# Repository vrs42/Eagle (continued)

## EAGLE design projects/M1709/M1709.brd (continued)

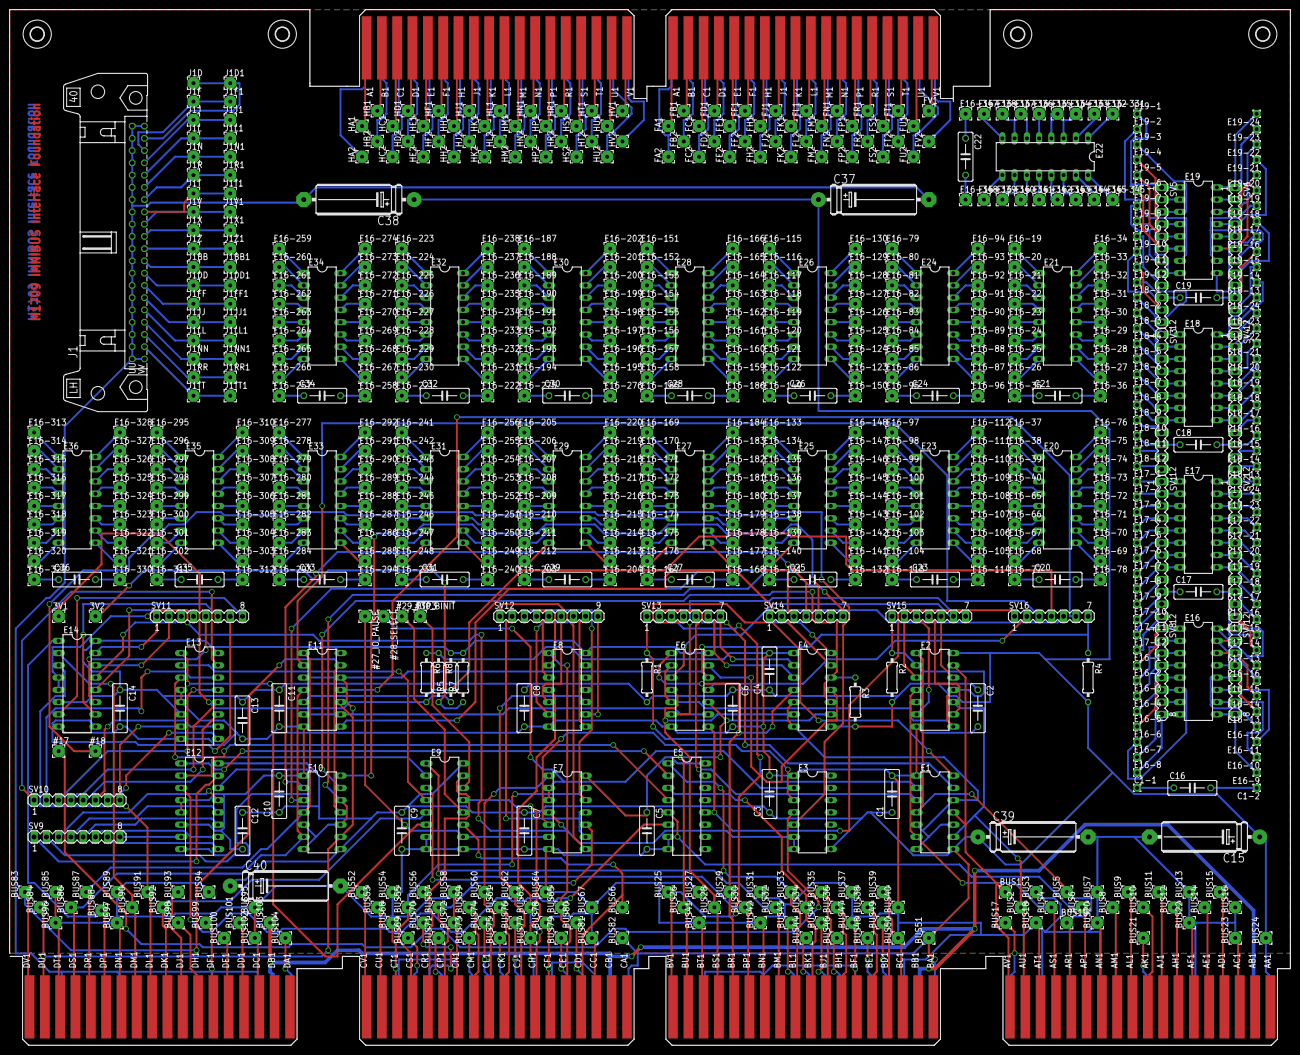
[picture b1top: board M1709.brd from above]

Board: 2 copper layers, 265.4 x 214.6 mm, 723 parts (0 on the bottom side), 633 nets.

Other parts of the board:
U$6, U$7, U$8, U$9: 2,8

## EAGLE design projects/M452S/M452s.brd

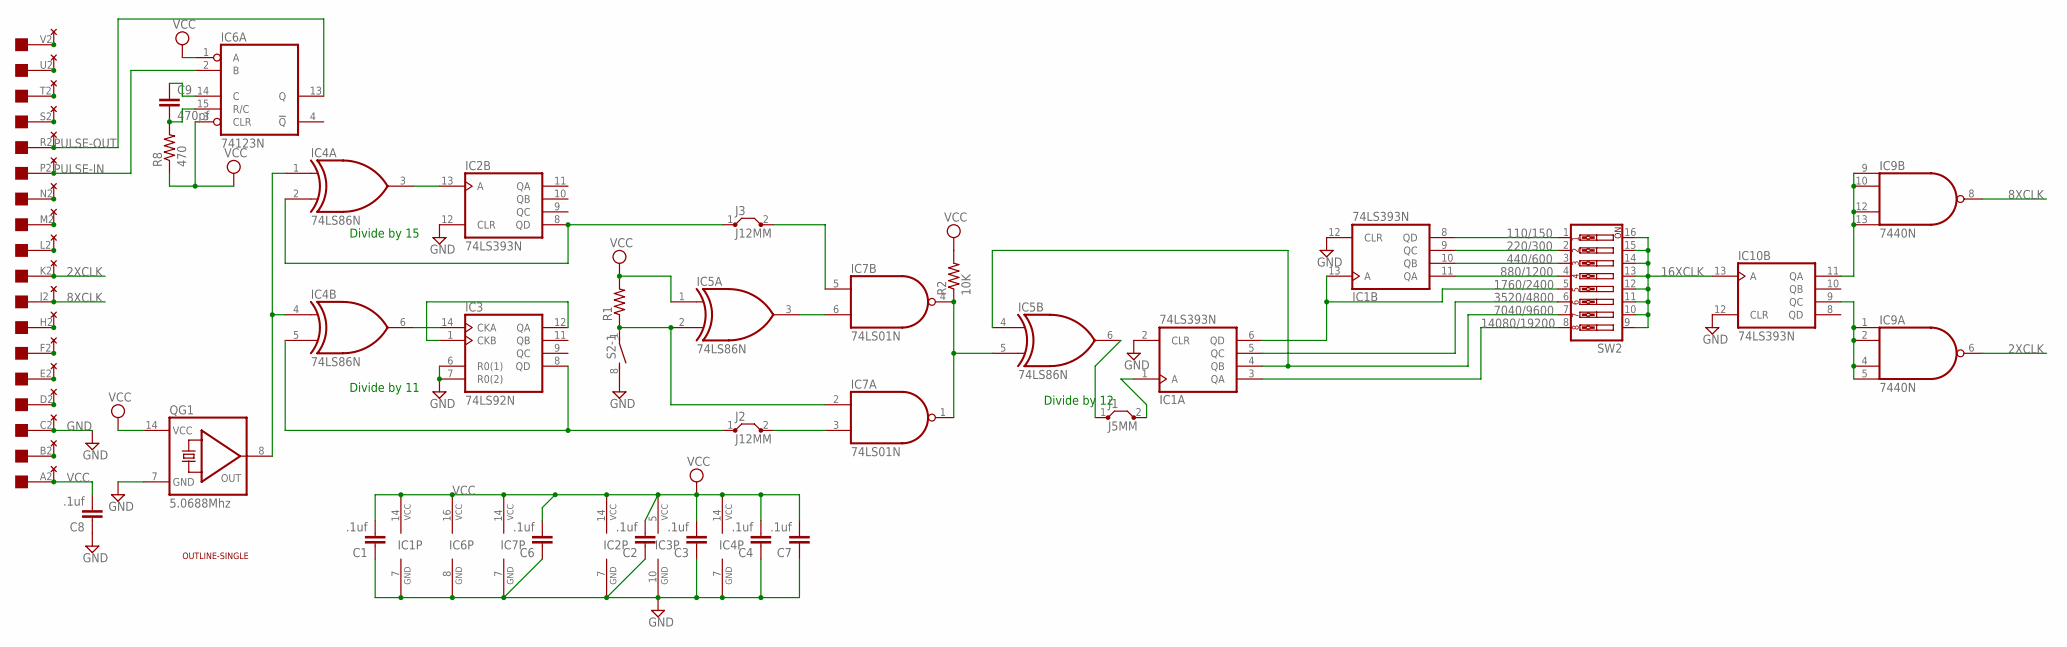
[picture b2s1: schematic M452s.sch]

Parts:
C1, C2, C3, C4, C6, C7, C8: .1uf; C050-025X075
C9: 470pf; C050-025X075
IC1, IC2, IC10: 74LS393N; DIL14
IC3: 74LS92N; DIL14
IC4, IC5: 74LS86N; DIL14
IC6: 74123N; DIL16
IC7: 74LS01N; DIL14
IC9: 7440N; DIL14
J1: J5MM; 05
J2, J3: J12MM; 12
QG1: 5.0688Mhz; DIL14S
R1: R-US_0204/7; 0204/7
R2: 10K; 0204/7
R8: 470; 0204/7
S2: DIP04S
SW2: SW_DIP-8; EDG-08
U$2: EDGE-1; EDGE-CON1
U$3: OUTLINE-SINGLE; SINGLE
U$4: THRU-HOLE1

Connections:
2XCLK: IC9.6 (O), U$2.K2, U$4.K2
8XCLK: IC9.8 (O), U$2.J2, U$4.J2
16XCLK: IC10.13 (A), SW2.9, SW2.10, SW2.11, SW2.12, SW2.13, SW2.14, SW2.15, SW2.16
110/150: IC1.8 (QD), SW2.1
220/300: IC1.9 (QC), SW2.2
440/600: IC1.10 (QB), SW2.3
880/1200: IC1.11 (QA), SW2.4
1760/2400: IC1.6 (QD), IC1.13 (A), SW2.5
3520/4800: IC1.5 (QC), SW2.6
7040/9600: IC1.4 (QB), IC5.4 (I0), SW2.7
14080/19200: IC1.3 (QA), SW2.8
GND: C1.1, C2.1, C3.1, C4.1, C6.1, C7.1, C8.1, IC1.2 (CLR), IC1.7 (GND), IC1.12 (CLR), IC2.7 (GND), IC2.12 (CLR), IC3.6 (R0(1)), IC3.7 (R0(2)), IC3.10 (GND), IC4.7 (GND), IC5.7 (GND), IC6.8 (GND), IC7.7 (GND), IC9.7 (GND), IC10.7 (GND), IC10.12 (CLR), QG1.7 (GND), S2.8 (2), U$2.C2, U$4.C2
unnamed: IC4.1 (I0), IC4.4 (I0), QG1.8 (OUT)
unnamed: IC2.8 (QD), IC4.2 (I1), J3.1
unnamed: IC3.8 (QD), IC4.5 (I1), J2.1
unnamed: IC3.1 (CKB), IC3.12 (QA)
unnamed: IC3.14 (CKA), IC4.6 (O)
unnamed: IC2.13 (A), IC4.3 (O)
unnamed: IC5.6 (O), J1.1
unnamed: IC5.2 (I1), IC7.2 (I0), R1.1, S2.1
unnamed: IC5.5 (I1), IC7.1 (O), IC7.4 (O), R2.1
unnamed: IC9.1 (I0), IC9.2 (I1), IC9.4 (I2), IC9.5 (I3), IC10.9 (QC)
unnamed: IC1.1 (A), J1.2
unnamed: IC9.9 (I0), IC9.10 (I1), IC9.12 (I2), IC9.13 (I3), IC10.11 (QA)
unnamed: IC7.5 (I0), J3.2
unnamed: IC7.3 (I1), J2.2
unnamed: IC5.3 (O), IC7.6 (I1)
unnamed: U$2.V2, U$4.V2
unnamed: U$2.U2, U$4.U2
unnamed: U$2.T2, U$4.T2
unnamed: U$2.S2, U$4.S2
unnamed: U$2.N2, U$4.N2
unnamed: C9.2, IC6.15 (R/C), R8.2
unnamed: C9.1, IC6.14 (C)
unnamed: U$2.M2, U$4.M2
unnamed: U$2.L2, U$4.L2
unnamed: U$2.H2, U$4.H2
unnamed: U$2.F2, U$4.F2
unnamed: U$2.E2, U$4.E2
unnamed: U$2.D2, U$4.D2
unnamed: U$2.B2, U$4.B2
PULSE-IN: IC6.2 (B), U$2.P2, U$4.P2
PULSE-OUT: IC6.13 (Q), U$2.R2, U$4.R2
VCC: C1.2, C2.2, C3.2, C4.2, C6.2, C7.2, C8.2, IC1.14 (VCC), IC2.14 (VCC), IC3.5 (VCC), IC4.14 (VCC), IC5.1 (I0), IC5.14 (VCC), IC6.1 (A), IC6.3 (CLR), IC6.16 (VCC), IC7.14 (VCC), IC9.14 (VCC), IC10.14 (VCC), QG1.14 (VCC), R1.2, R2.2, R8.1, U$2.A2, U$4.A2

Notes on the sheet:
Divide by 11
Divide by 15
Divide by 12

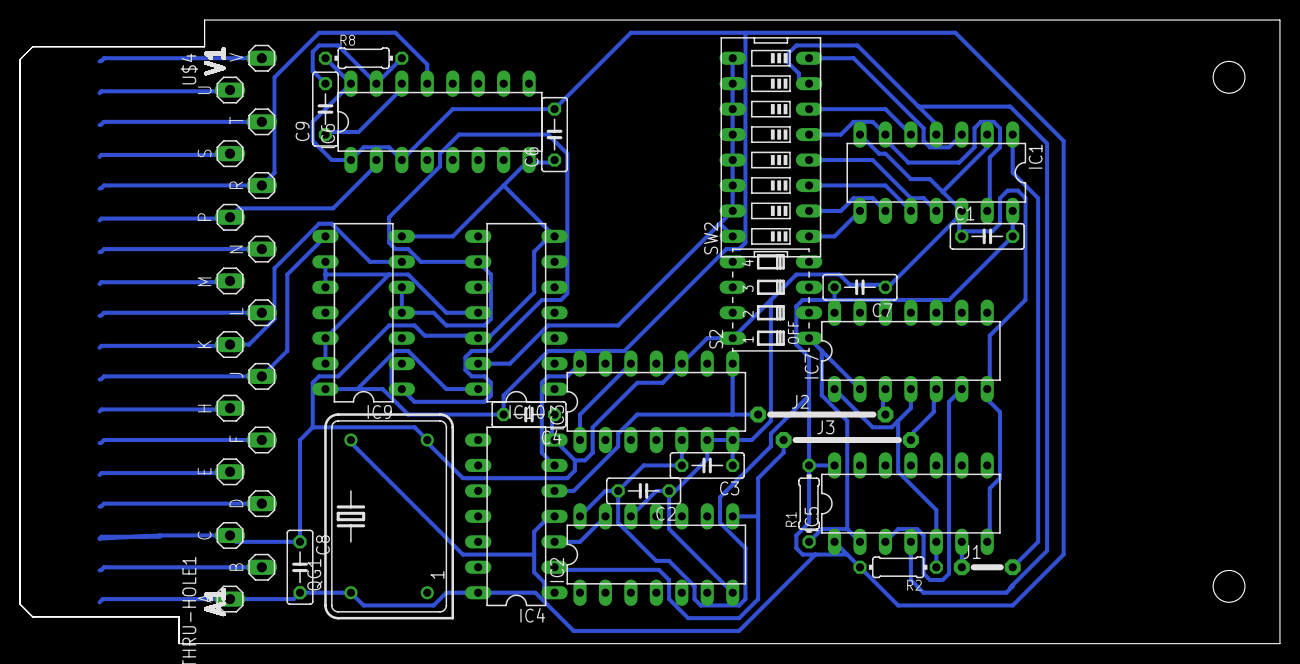
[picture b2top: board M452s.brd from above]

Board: 2 copper layers, 125.7 x 62.2 mm, 29 parts (0 on the bottom side), 44 nets.

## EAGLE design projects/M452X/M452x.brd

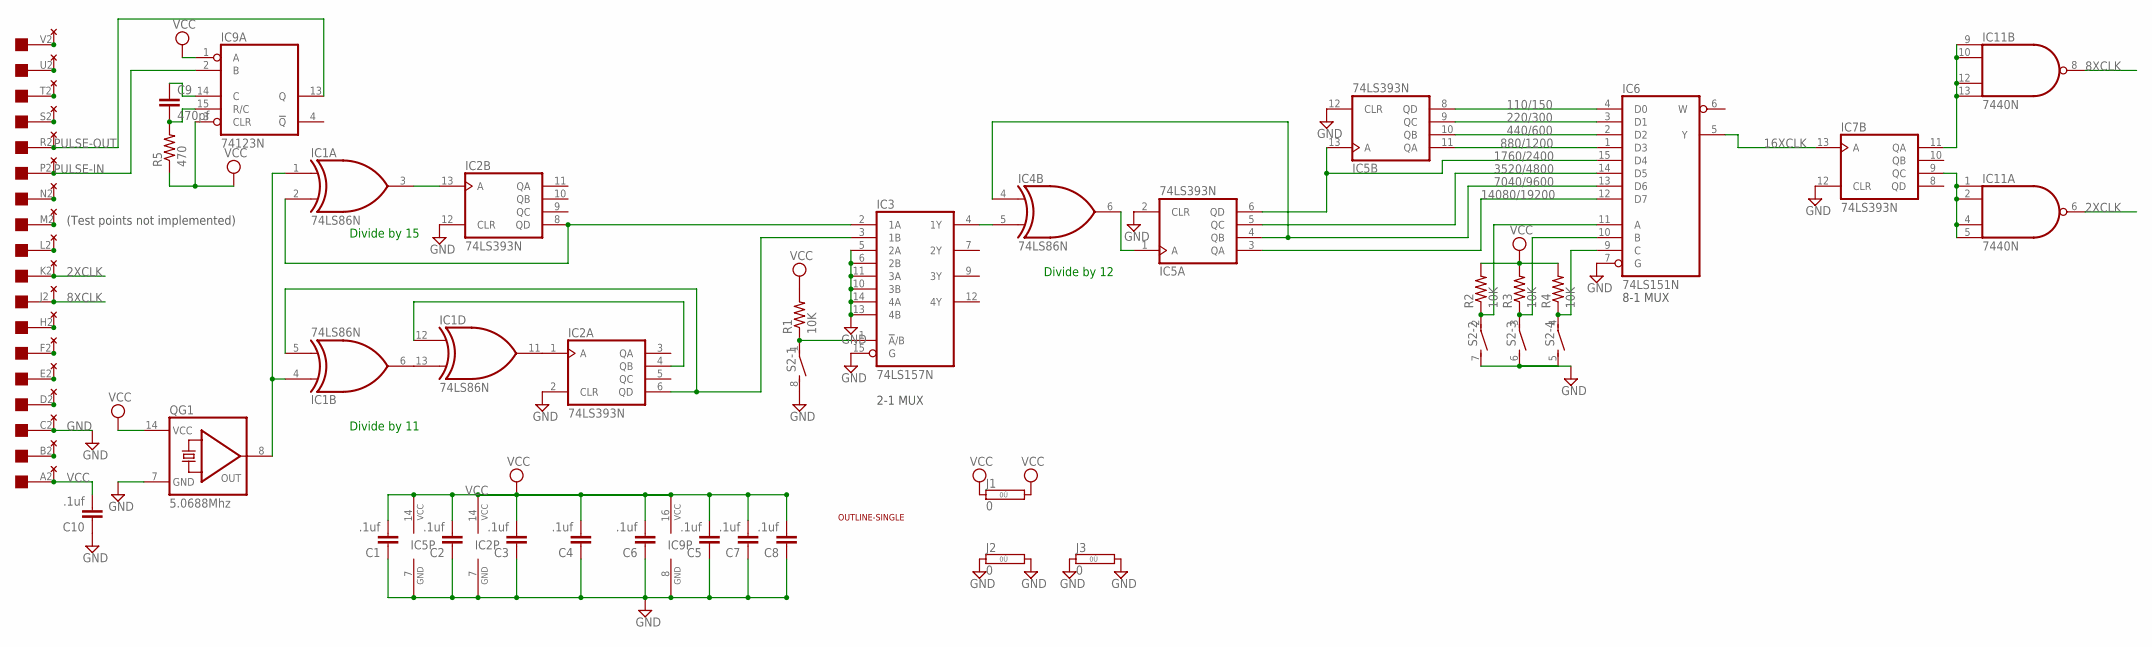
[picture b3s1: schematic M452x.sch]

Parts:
C1, C2, C3, C4, C5, C6, C7, C8, C10: .1uf; C050-025X075
C9: 470pf; C050-025X075
IC1, IC4: 74LS86N; DIL14
IC2, IC5, IC7: 74LS393N; DIL14
IC3: 74LS157N; DIL16
IC6: 74LS151N; DIL16
IC9: 74123N; DIL16
IC11: 7440N; DIL14
J1, J2, J3: 0; 0R/10
QG1: 5.0688Mhz; DIL14S
R1, R2, R3, R4: 10K; 0204/7
R5: 470; 0204/7
S2: DIP04S
U$2: THRU-HOLE1
U$3: OUTLINE-SINGLE; SINGLE
U$4: EDGE-1; EDGE-CON1

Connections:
2XCLK: IC11.6 (O), U$2.K2, U$4.K2
8XCLK: IC11.8 (O), U$2.J2, U$4.J2
16XCLK: IC6.5 (Y), IC7.13 (A)
110/150: IC5.8 (QD), IC6.4 (D0)
220/300: IC5.9 (QC), IC6.3 (D1)
440/600: IC5.10 (QB), IC6.2 (D2)
880/1200: IC5.11 (QA), IC6.1 (D3)
1760/2400: IC5.6 (QD), IC5.13 (A), IC6.15 (D4)
3520/4800: IC5.5 (QC), IC6.14 (D5)
7040/9600: IC4.4 (I0), IC5.4 (QB), IC6.13 (D6)
14080/19200: IC5.3 (QA), IC6.12 (D7)
GND: C1.1, C2.1, C3.1, C4.1, C5.1, C6.1, C7.1, C8.1, C10.1, IC1.7 (GND), IC2.2 (CLR), IC2.7 (GND), IC2.12 (CLR), IC3.5 (2A), IC3.6 (2B), IC3.8 (GND), IC3.10 (3B), IC3.11 (3A), IC3.13 (4B), IC3.14 (4A), IC3.15 (G), IC4.7 (GND), IC5.2 (CLR), IC5.7 (GND), IC5.12 (CLR), IC6.7 (G), IC6.8 (GND), IC7.7 (GND), IC7.12 (CLR), IC9.8 (GND), IC11.7 (GND), J2.1, J2.2, J3.1, J3.2, QG1.7 (GND), S2.5 (2), S2.6 (2), S2.7 (2), S2.8 (2), U$2.C2, U$4.C2
unnamed: IC1.1 (I0), IC1.4 (I0), QG1.8 (OUT)
unnamed: IC1.2 (I1), IC2.8 (QD), IC3.2 (1A)
unnamed: IC1.5 (I1), IC2.6 (QD), IC3.3 (1B)
unnamed: U$2.V2, U$4.V2
unnamed: U$2.U2, U$4.U2
unnamed: IC1.3 (O), IC2.13 (A)
unnamed: IC1.11 (O), IC2.1 (A)
unnamed: IC6.11 (A), R2.1, S2.2 (1)
unnamed: IC3.4 (1Y), IC4.5 (I1)
unnamed: IC7.9 (QC), IC11.1 (I0), IC11.2 (I1), IC11.4 (I2), IC11.5 (I3)
unnamed: IC4.6 (O), IC5.1 (A)
unnamed: IC7.11 (QA), IC11.9 (I0), IC11.10 (I1), IC11.12 (I2), IC11.13 (I3)
unnamed: IC6.10 (B), R3.1, S2.3 (1)
unnamed: IC6.9 (C), R4.1, S2.4 (1)
unnamed: IC1.6 (O), IC1.13 (I1)
unnamed: U$2.T2, U$4.T2
unnamed: IC3.1 (!A!/B), R1.1, S2.1
unnamed: U$2.S2, U$4.S2
unnamed: IC1.12 (I0), IC2.4 (QB)
unnamed: U$2.N2, U$4.N2
unnamed: C9.2, IC9.15 (R/C), R5.2
unnamed: C9.1, IC9.14 (C)
unnamed: U$2.M2, U$4.M2
unnamed: U$2.L2, U$4.L2
unnamed: U$2.H2, U$4.H2
unnamed: U$2.F2, U$4.F2
unnamed: U$2.E2, U$4.E2
unnamed: U$2.D2, U$4.D2
unnamed: U$2.B2, U$4.B2
PULSE-IN: IC9.2 (B), U$2.P2, U$4.P2
PULSE-OUT: IC9.13 (Q), U$2.R2, U$4.R2
VCC: C1.2, C2.2, C3.2, C4.2, C5.2, C6.2, C7.2, C8.2, C10.2, IC1.14 (VCC), IC2.14 (VCC), IC3.16 (VCC), IC4.14 (VCC), IC5.14 (VCC), IC6.16 (VCC), IC7.14 (VCC), IC9.1 (A), IC9.3 (CLR), IC9.16 (VCC), IC11.14 (VCC), J1.1, J1.2, QG1.14 (VCC), R1.2, R2.2, R3.2, R4.2, R5.1, U$2.A2, U$4.A2

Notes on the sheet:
Divide by 11
Divide by 15
Divide by 12
(Test points not implemented)
2-1 MUX
8-1 MUX

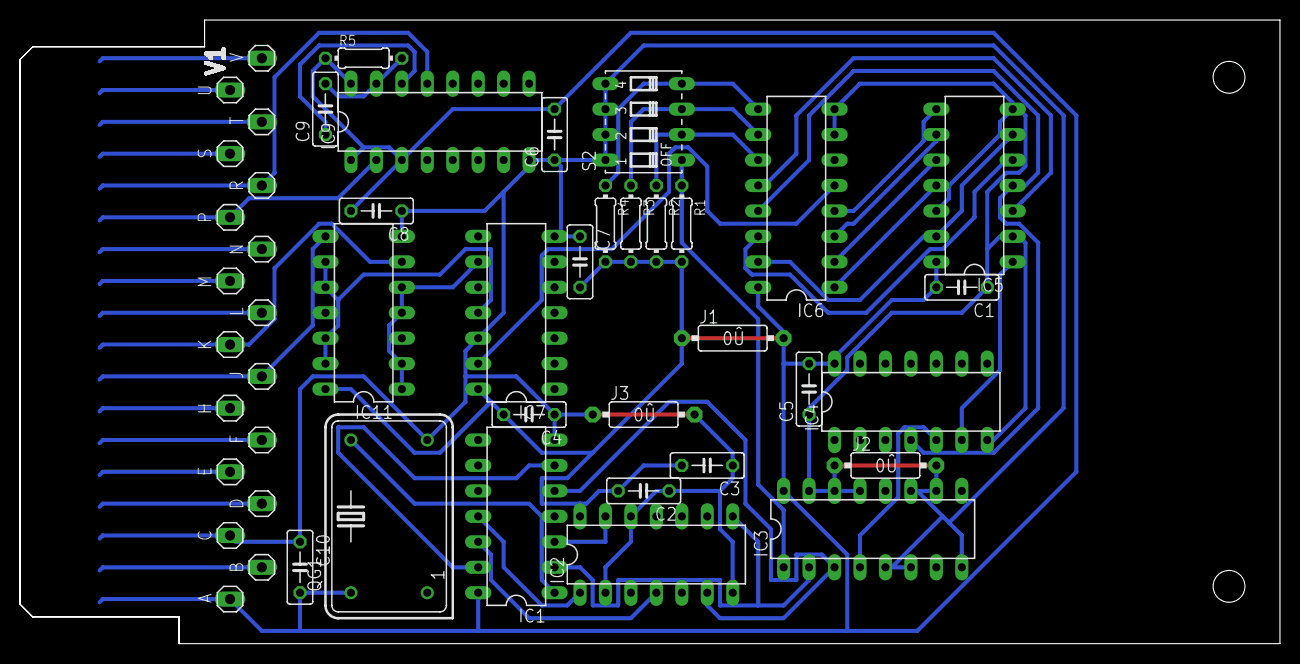
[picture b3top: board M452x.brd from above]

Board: 2 copper layers, 125.7 x 62.2 mm, 32 parts (0 on the bottom side), 44 nets.

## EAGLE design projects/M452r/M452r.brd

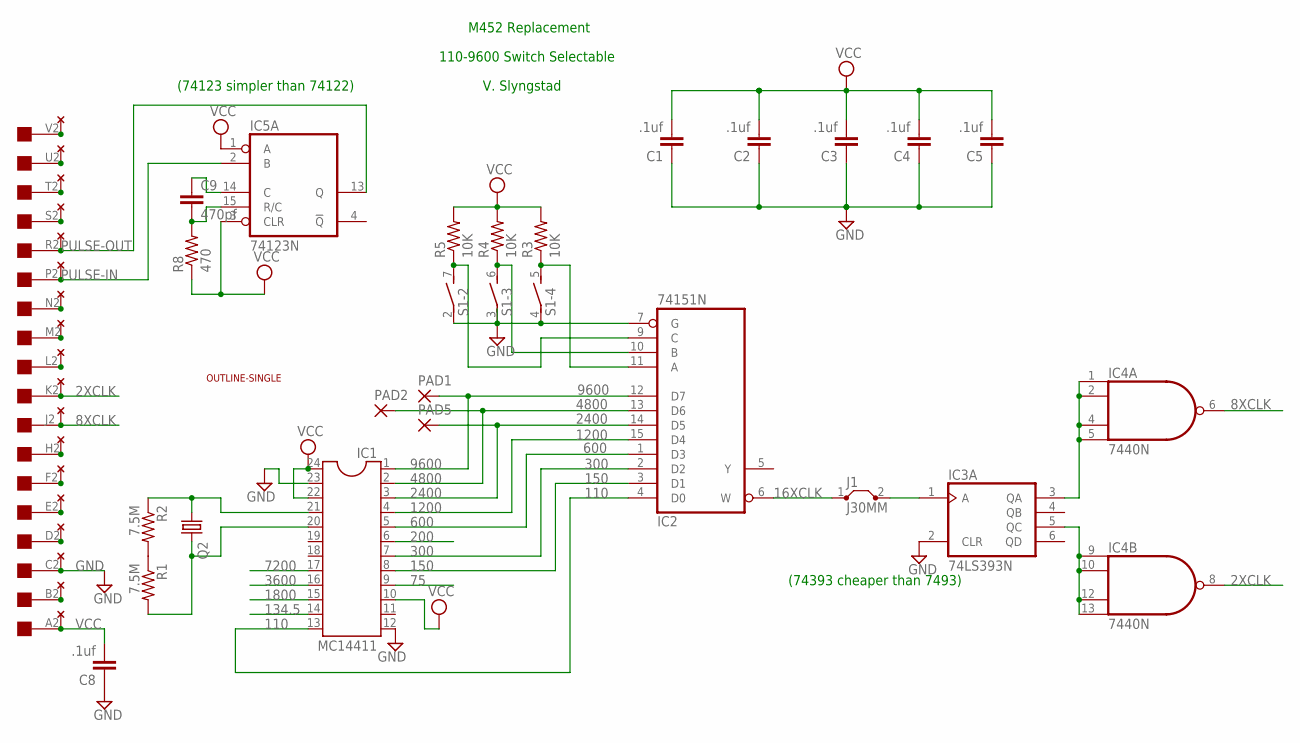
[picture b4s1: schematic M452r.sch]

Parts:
C1, C2, C3, C4, C5, C8: .1uf; C050-025X075
C9: 470pf; C050-025X075
IC1: MC14411; DIL24-6
IC2: 74151N; DIL16
IC3: 74LS393N; DIL14
IC4: 7440N; DIL14
IC5: 74123N; DIL16
J1: J30MM; 30
PAD1, PAD2, PAD5: 1,6/0,8
Q2: CRYSTALHC49U-H; HC49U-H
R1, R2: 7.5M; 0204/7
R3, R4, R5: 10K; 0204/7
R8: 470; 0204/7
S1: DIP04S
U$2: EDGE-1; EDGE-CON1
U$3: THRU-HOLE1
U$4: OUTLINE-SINGLE; SINGLE

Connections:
2XCLK: IC4.8 (O), U$2.K2, U$3.K2
8XCLK: IC4.6 (O), U$2.J2, U$3.J2
16XCLK: IC2.6 (W), J1.1
75: IC1.9
110: IC1.13, IC2.4 (D0)
134.5: IC1.14
150: IC1.8, IC2.3 (D1)
200: IC1.6
300: IC1.7, IC2.2 (D2)
600: IC1.5, IC2.1 (D3)
1200: IC1.4, IC2.15 (D4)
1800: IC1.15
2400: IC1.3, IC2.14 (D5), PAD5.1
3600: IC1.16
4800: IC1.2, IC2.13 (D6), PAD2.1
7200: IC1.17
9600: IC1.1, IC2.12 (D7), PAD1.1
GND: C1.1, C2.1, C3.1, C4.1, C5.1, C8.1, IC1.12, IC1.23, IC2.7 (G), IC2.8 (GND), IC3.2 (CLR), IC3.7 (GND), IC4.7 (GND), IC5.8 (GND), S1.2 (1), S1.3 (1), S1.4 (1), U$2.C2, U$3.C2
unnamed: IC1.20, Q2.2, R1.2
unnamed: IC2.9 (C), R5.1, S1.7 (2)
unnamed: R1.1, R2.2
unnamed: IC3.1 (A), J1.2
unnamed: U$2.V2, U$3.V2
unnamed: U$2.U2, U$3.U2
unnamed: U$2.T2, U$3.T2
unnamed: U$2.S2, U$3.S2
unnamed: U$2.N2, U$3.N2
unnamed: IC3.5 (QC), IC4.9 (I0), IC4.10 (I1), IC4.12 (I2), IC4.13 (I3)
unnamed: U$2.M2, U$3.M2
unnamed: IC3.3 (QA), IC4.1 (I0), IC4.2 (I1), IC4.4 (I2), IC4.5 (I3)
unnamed: U$2.L2, U$3.L2
unnamed: U$2.H2, U$3.H2
unnamed: U$2.F2, U$3.F2
unnamed: U$2.E2, U$3.E2
unnamed: IC2.11 (A), R3.1, S1.5 (2)
unnamed: IC1.21, Q2.1, R2.1
unnamed: U$2.D2, U$3.D2
unnamed: IC2.10 (B), R4.1, S1.6 (2)
unnamed: C9.2, IC5.15 (R/C), R8.2
unnamed: C9.1, IC5.14 (C)
unnamed: U$2.B2, U$3.B2
PULSE-IN: IC5.2 (B), U$2.P2, U$3.P2
PULSE-OUT: IC5.13 (Q), U$2.R2, U$3.R2
VCC: C1.2, C2.2, C3.2, C4.2, C5.2, C8.2, IC1.10, IC1.22, IC1.24, IC2.16 (VCC), IC3.14 (VCC), IC4.14 (VCC), IC5.1 (A), IC5.3 (CLR), IC5.16 (VCC), R3.2, R4.2, R5.2, R8.1, U$2.A2, U$3.A2

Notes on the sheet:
(74393 cheaper than 7493)
(74123 simpler than 74122)
M452 Replacement
110-9600 Switch Selectable
V. Slyngstad

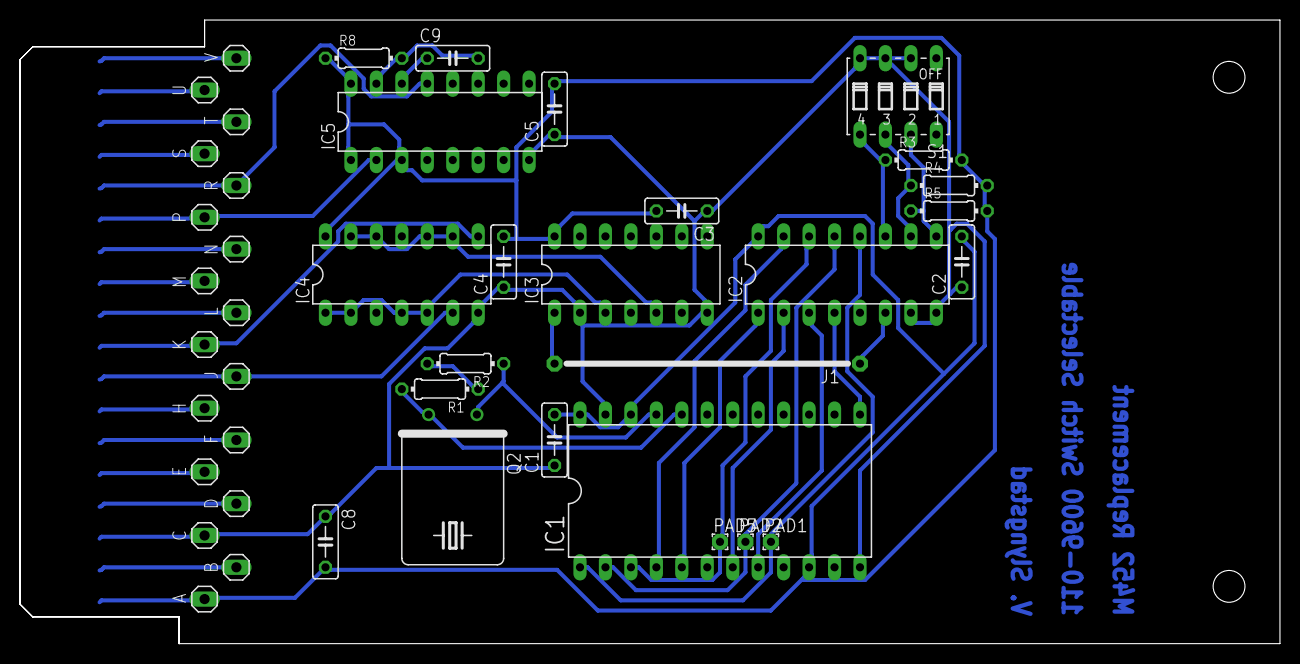
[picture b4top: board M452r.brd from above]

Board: 2 copper layers, 125.7 x 62.2 mm, 27 parts (0 on the bottom side), 38 nets.

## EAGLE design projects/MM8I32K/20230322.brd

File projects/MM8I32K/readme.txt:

Vincent Slyngstad

Please build a quantity of 5 pieces of this 2-layer board. We are requesting
1-oz. finished copper weight, 0.062" thick on FR4 material.

The Gerber files included in this zip:

File Name Description:
20230322.otl Board Outline
20230322.cmp Layer 1 (component side) 
20230322.sol Layer 2 solder side
20230322.stc Component-side solder mask
20230322.sts Solder-side solder mask
20230322.plc Component-side silkscreen (nomenclature)
20230322.drd Excellon drill file
20230322.drl Drill tool description 

Any technical questions can be referred to vincent.slyngstad@gmail.com
My contact number is 503-259-9615.

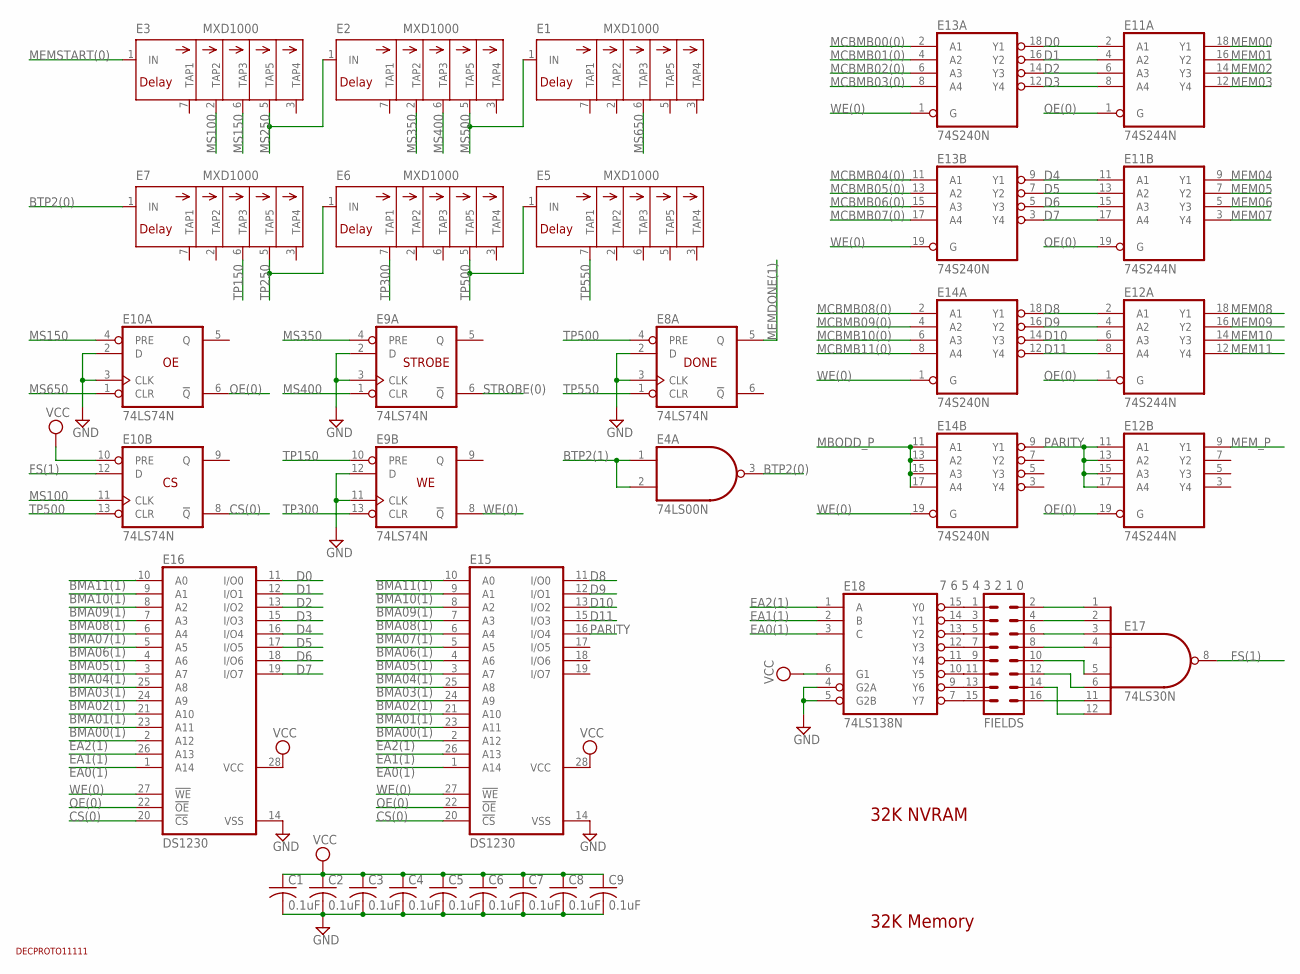
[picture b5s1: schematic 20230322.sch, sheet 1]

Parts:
C1, C2, C3, C4, C5, C6, C7, C8, C9: 0.1uF; C050-025X075
E1, E2, E3, E5, E6, E7: MXD1000; DIL08
E4: 74LS00N; DIL14
E8, E9, E10: 74LS74N; DIL14
E11, E12: 74S244N; DIL20
E13, E14: 74S240N; DIL20
E15, E16: DS1230; DIL28-6
E17: 74LS30N; DIL14
E18: 74LS138N; DIL16
FIELDS: 7 6 5 4 3 2 1 0; MA08-2
U$6: DECPROTO11111

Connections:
BMA00(1): E15.23 (A11), E16.23 (A11); also elsewhere on the board
BMA01(1): E15.21 (A10), E16.21 (A10); also elsewhere on the board
BMA02(1): E15.24 (A9), E16.24 (A9); also elsewhere on the board
BMA03(1): E15.25 (A8), E16.25 (A8); also elsewhere on the board
BMA04(1): E15.3 (A7), E16.3 (A7); also elsewhere on the board
BMA05(1): E15.4 (A6), E16.4 (A6); also elsewhere on the board
BMA06(1): E15.5 (A5), E16.5 (A5); also elsewhere on the board
BMA07(1): E15.6 (A4), E16.6 (A4); also elsewhere on the board
BMA08(1): E15.7 (A3), E16.7 (A3); also elsewhere on the board
BMA09(1): E15.8 (A2), E16.8 (A2); also elsewhere on the board
BMA10(1): E15.9 (A1), E16.9 (A1); also elsewhere on the board
BMA11(1): E15.10 (A0), E16.10 (A0); also elsewhere on the board
BTP2(0): E4.3 (O), E7.1 (IN)
BTP2(1): E4.1 (I0), E4.2 (I1); also elsewhere on the board
CS(0): E10.8 (!Q), E15.20 (!CS), E16.20 (!CS); also elsewhere on the board
D0: E11.2 (A1), E13.18 (Y1), E16.11 (I/O0); also elsewhere on the board
D1: E11.4 (A2), E13.16 (Y2), E16.12 (I/O1); also elsewhere on the board
D2: E11.6 (A3), E13.14 (Y3), E16.13 (I/O2); also elsewhere on the board
D3: E11.8 (A4), E13.12 (Y4), E16.15 (I/O3); also elsewhere on the board
D4: E11.11 (A1), E13.9 (Y1), E16.16 (I/O4); also elsewhere on the board
D5: E11.13 (A2), E13.7 (Y2), E16.17 (I/O5); also elsewhere on the board
D6: E11.15 (A3), E13.5 (Y3), E16.18 (I/O6); also elsewhere on the board
D7: E11.17 (A4), E13.3 (Y4), E16.19 (I/O7); also elsewhere on the board
D8: E12.2 (A1), E14.18 (Y1), E15.11 (I/O0); also elsewhere on the board
D9: E12.4 (A2), E14.16 (Y2), E15.12 (I/O1); also elsewhere on the board
D10: E12.6 (A3), E14.14 (Y3), E15.13 (I/O2); also elsewhere on the board
D11: E12.8 (A4), E14.12 (Y4), E15.15 (I/O3); also elsewhere on the board
EA0(1): E15.1 (A14), E16.1 (A14), E18.3 (C); also elsewhere on the board
EA1(1): E15.26 (A13), E16.26 (A13), E18.2 (B); also elsewhere on the board
EA2(1): E15.2 (A12), E16.2 (A12), E18.1 (A); also elsewhere on the board
FS(1): E10.12 (D), E17.8 (O); also elsewhere on the board
GND: C1.2, C2.2, C3.2, C4.2, C5.2, C6.2, C7.2, C8.2, C9.2, E1.4 (GND), E2.4 (GND), E3.4 (GND), E4.7 (GND), E5.4 (GND), E6.4 (GND), E7.4 (GND), E8.2 (D), E8.3 (CLK), E8.7 (GND), E9.2 (D), E9.3 (CLK), E9.7 (GND), E9.11 (CLK), E9.12 (D), E10.2 (D), E10.3 (CLK), E10.7 (GND), E11.10 (GND), E12.10 (GND), E13.10 (GND), E14.10 (GND), E15.14 (VSS), E16.14 (VSS), E17.7 (GND), E18.4 (G2A), E18.5 (G2B), E18.8 (GND); also elsewhere on the board
MBODD_P: E14.11 (A1), E14.13 (A2), E14.15 (A3), E14.17 (A4); also elsewhere on the board
MCBMB00(0): E13.2 (A1); also elsewhere on the board
MCBMB01(0): E13.4 (A2); also elsewhere on the board
MCBMB02(0): E13.6 (A3); also elsewhere on the board
MCBMB03(0): E13.8 (A4); also elsewhere on the board
MCBMB04(0): E13.11 (A1); also elsewhere on the board
MCBMB05(0): E13.13 (A2); also elsewhere on the board
MCBMB06(0): E13.15 (A3); also elsewhere on the board
MCBMB07(0): E13.17 (A4); also elsewhere on the board
MCBMB08(0): E14.2 (A1); also elsewhere on the board
MCBMB09(0): E14.4 (A2); also elsewhere on the board
MCBMB10(0): E14.6 (A3); also elsewhere on the board
MCBMB11(0): E14.8 (A4); also elsewhere on the board
MEM00: E11.18 (Y1); also elsewhere on the board
MEM01: E11.16 (Y2); also elsewhere on the board
MEM02: E11.14 (Y3); also elsewhere on the board
MEM03: E11.12 (Y4); also elsewhere on the board
MEM04: E11.9 (Y1); also elsewhere on the board
MEM05: E11.7 (Y2); also elsewhere on the board
MEM06: E11.5 (Y3); also elsewhere on the board
MEM07: E11.3 (Y4); also elsewhere on the board
MEM08: E12.18 (Y1); also elsewhere on the board
MEM09: E12.16 (Y2); also elsewhere on the board
MEM10: E12.14 (Y3); also elsewhere on the board
MEM11: E12.12 (Y4); also elsewhere on the board
MEMDONE(1): E8.5 (Q); also elsewhere on the board
MEMSTART(0): E3.1 (IN); also elsewhere on the board
MEM_P: E12.9 (Y1); also elsewhere on the board
MS100: E3.2 (TAP2), E10.11 (CLK)
MS150: E3.6 (TAP3), E10.4 (PRE)
MS250: E2.1 (IN), E3.5 (TAP5)
MS350: E2.2 (TAP2), E9.4 (PRE)
MS400: E2.6 (TAP3), E9.1 (CLR)
MS500: E1.1 (IN), E2.5 (TAP5)
MS650: E1.6 (TAP3), E10.1 (CLR)
unnamed: E18.15 (Y0), FIELDS.1
unnamed: E18.14 (Y1), FIELDS.3
unnamed: E18.13 (Y2), FIELDS.5
unnamed: E18.12 (Y3), FIELDS.7
unnamed: E18.11 (Y4), FIELDS.9
unnamed: E18.10 (Y5), FIELDS.11
unnamed: E18.9 (Y6), FIELDS.13
unnamed: E18.7 (Y7), FIELDS.15
unnamed: E17.4 (I3), FIELDS.8
unnamed: E17.3 (I2), FIELDS.6
unnamed: E17.2 (I1), FIELDS.4
unnamed: E17.1 (I0), FIELDS.2
unnamed: E17.5 (I4), FIELDS.10
unnamed: E17.6 (I5), FIELDS.12
unnamed: E17.12 (I7), FIELDS.14
unnamed: E17.11 (I6), FIELDS.16
OE(0): E10.6 (!Q), E11.1 (G), E11.19 (G), E12.1 (G), E12.19 (G), E15.22 (!OE), E16.22 (!OE); also elsewhere on the board
PARITY: E12.11 (A1), E12.13 (A2), E12.15 (A3), E12.17 (A4), E14.9 (Y1), E15.16 (I/O4); also elsewhere on the board
STROBE(0): E9.6 (!Q); also elsewhere on the board
TP150: E7.6 (TAP3), E9.10 (PRE)
TP250: E6.1 (IN), E7.5 (TAP5)
TP300: E6.7 (TAP1), E9.13 (CLR)
TP500: E5.1 (IN), E6.5 (TAP5), E8.4 (PRE), E10.13 (CLR)
TP550: E5.7 (TAP1), E8.1 (CLR)
VCC: C1.1, C2.1, C3.1, C4.1, C5.1, C6.1, C7.1, C8.1, C9.1, E1.8 (VCC), E2.8 (VCC), E3.8 (VCC), E4.14 (VCC), E5.8 (VCC), E6.8 (VCC), E7.8 (VCC), E8.14 (VCC), E9.14 (VCC), E10.10 (PRE), E10.14 (VCC), E11.20 (VCC), E12.20 (VCC), E13.20 (VCC), E14.20 (VCC), E15.28 (VCC), E16.28 (VCC), E17.14 (VCC), E18.6 (G1), E18.16 (VCC); also elsewhere on the board
WE(0): E9.8 (!Q), E13.1 (G), E13.19 (G), E14.1 (G), E14.19 (G), E15.27 (!WE), E16.27 (!WE); also elsewhere on the board

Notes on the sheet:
32K NVRAM
32K Memory
STROBE
DONE

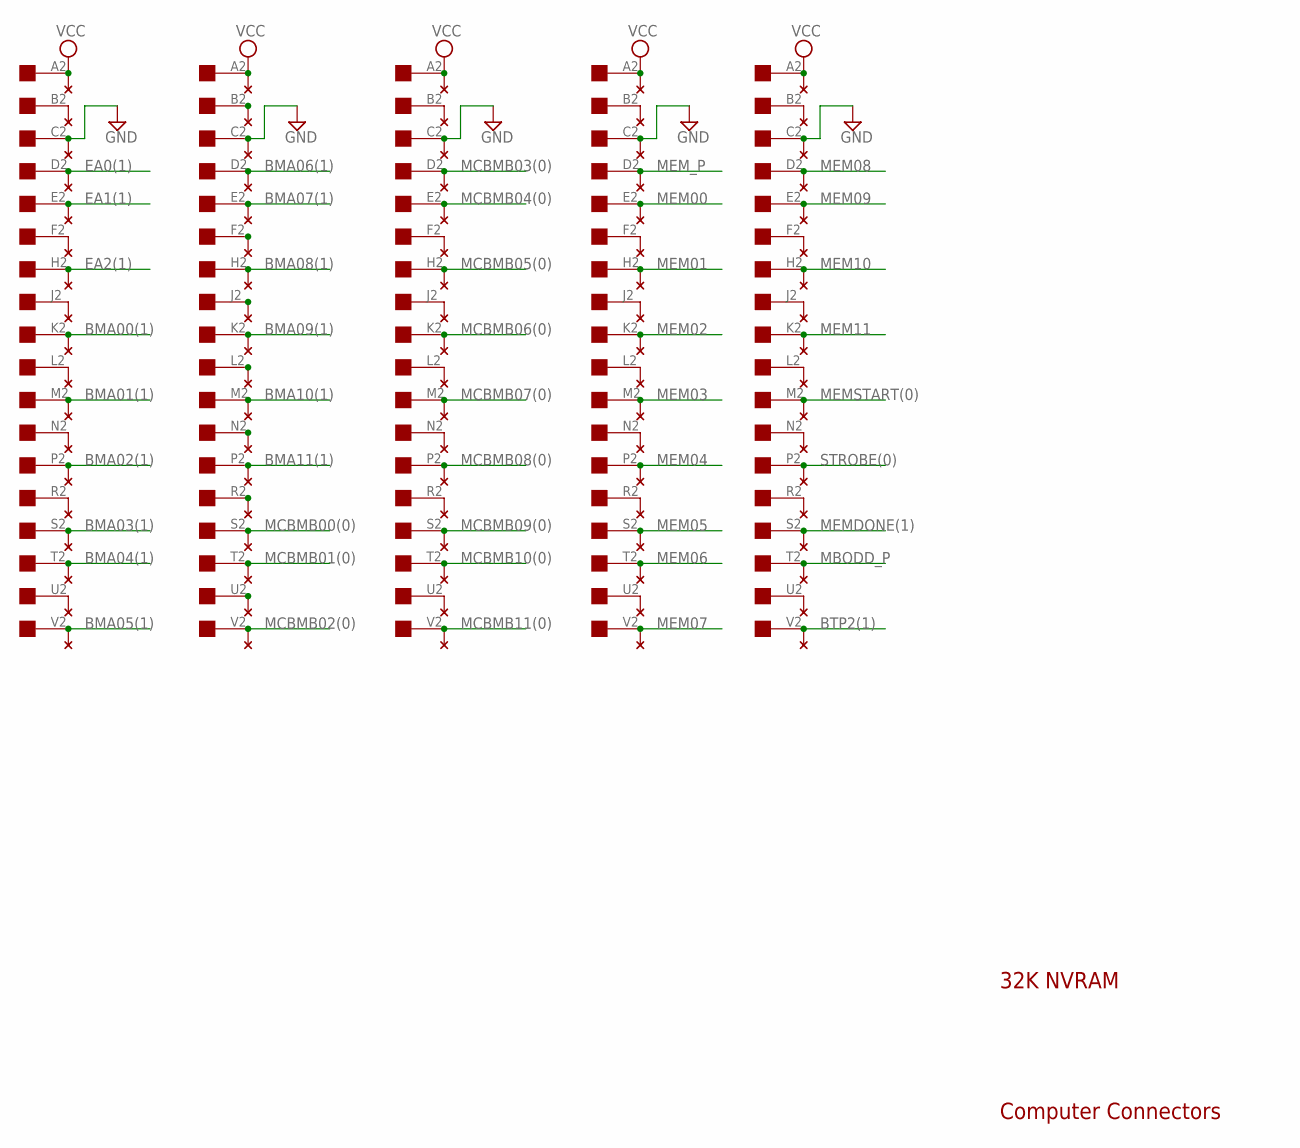
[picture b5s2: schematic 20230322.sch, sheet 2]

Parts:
H01, H02, H03, H04, H05: EDGE-CON1
U$1, U$2, U$3, U$4, U$5: THRU-HOLE2; THRU-HOLEB

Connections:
BMA00(1): H01.K2, U$1.K2; also elsewhere on the board
BMA01(1): H01.M2, U$1.M2; also elsewhere on the board
BMA02(1): H01.P2, U$1.P2; also elsewhere on the board
BMA03(1): H01.S2, U$1.S2; also elsewhere on the board
BMA04(1): H01.T2, U$1.T2; also elsewhere on the board
BMA05(1): H01.V2, U$1.V2; also elsewhere on the board
BMA06(1): H02.D2, U$2.D2; also elsewhere on the board
BMA07(1): H02.E2, U$2.E2; also elsewhere on the board
BMA08(1): H02.H2, U$2.H2; also elsewhere on the board
BMA09(1): H02.K2, U$2.K2; also elsewhere on the board
BMA10(1): H02.M2, U$2.M2; also elsewhere on the board
BMA11(1): H02.P2, U$2.P2; also elsewhere on the board
BTP2(1): H05.V2, U$5.V2; also elsewhere on the board
EA0(1): H01.D2, U$1.D2; also elsewhere on the board
EA1(1): H01.E2, U$1.E2; also elsewhere on the board
EA2(1): H01.H2, U$1.H2; also elsewhere on the board
GND: H01.C2, H02.C2, H03.C2, H04.C2, H05.C2, U$1.C2, U$2.C2, U$3.C2, U$4.C2, U$5.C2; also elsewhere on the board
MBODD_P: H05.T2, U$5.T2; also elsewhere on the board
MCBMB00(0): H02.S2, U$2.S2; also elsewhere on the board
MCBMB01(0): H02.T2, U$2.T2; also elsewhere on the board
MCBMB02(0): H02.V2, U$2.V2; also elsewhere on the board
MCBMB03(0): H03.D2, U$3.D2; also elsewhere on the board
MCBMB04(0): H03.E2, U$3.E2; also elsewhere on the board
MCBMB05(0): H03.H2, U$3.H2; also elsewhere on the board
MCBMB06(0): H03.K2, U$3.K2; also elsewhere on the board
MCBMB07(0): H03.M2, U$3.M2; also elsewhere on the board
MCBMB08(0): H03.P2, U$3.P2; also elsewhere on the board
MCBMB09(0): H03.S2, U$3.S2; also elsewhere on the board
MCBMB10(0): H03.T2, U$3.T2; also elsewhere on the board
MCBMB11(0): H03.V2, U$3.V2; also elsewhere on the board
MEM00: H04.E2, U$4.E2; also elsewhere on the board
MEM01: H04.H2, U$4.H2; also elsewhere on the board
MEM02: H04.K2, U$4.K2; also elsewhere on the board
MEM03: H04.M2, U$4.M2; also elsewhere on the board
MEM04: H04.P2, U$4.P2; also elsewhere on the board
MEM05: H04.S2, U$4.S2; also elsewhere on the board
MEM06: H04.T2, U$4.T2; also elsewhere on the board
MEM07: H04.V2, U$4.V2; also elsewhere on the board
MEM08: H05.D2, U$5.D2; also elsewhere on the board
MEM09: H05.E2, U$5.E2; also elsewhere on the board
MEM10: H05.H2, U$5.H2; also elsewhere on the board
MEM11: H05.K2, U$5.K2; also elsewhere on the board
MEMDONE(1): H05.S2, U$5.S2; also elsewhere on the board
MEMSTART(0): H05.M2, U$5.M2; also elsewhere on the board
MEM_P: H04.D2, U$4.D2; also elsewhere on the board
unnamed: H01.L2, U$1.L2
unnamed: H01.N2, U$1.N2
unnamed: H01.R2, U$1.R2
unnamed: H02.L2, U$2.L2
unnamed: H02.N2, U$2.N2
unnamed: H01.J2, U$1.J2
unnamed: H02.R2, U$2.R2
unnamed: H01.F2, U$1.F2
unnamed: H02.J2, U$2.J2
unnamed: H02.F2, U$2.F2
unnamed: H02.U2, U$2.U2
unnamed: H01.U2, U$1.U2
unnamed: H02.B2, U$2.B2
unnamed: H01.B2, U$1.B2
unnamed: H04.J2, U$4.J2
unnamed: H04.L2, U$4.L2
unnamed: H04.N2, U$4.N2
unnamed: H03.J2, U$3.J2
unnamed: H03.L2, U$3.L2
unnamed: H03.N2, U$3.N2
unnamed: H03.F2, U$3.F2
unnamed: H03.R2, U$3.R2
unnamed: H03.B2, U$3.B2
unnamed: H03.U2, U$3.U2
unnamed: H05.J2, U$5.J2
unnamed: H05.L2, U$5.L2
unnamed: H05.N2, U$5.N2
unnamed: H05.F2, U$5.F2
unnamed: H05.R2, U$5.R2
unnamed: H05.B2, U$5.B2
unnamed: H05.U2, U$5.U2
unnamed: H04.F2, U$4.F2
unnamed: H04.R2, U$4.R2
unnamed: H04.B2, U$4.B2
unnamed: H04.U2, U$4.U2
STROBE(0): H05.P2, U$5.P2; also elsewhere on the board
VCC: H01.A2, H02.A2, H03.A2, H04.A2, H05.A2, U$1.A2, U$2.A2, U$3.A2, U$4.A2, U$5.A2; also elsewhere on the board

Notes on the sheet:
32K NVRAM
Computer Connectors
